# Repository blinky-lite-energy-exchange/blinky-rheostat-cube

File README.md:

# Blinky Rheostat Cube
The Blinky Rheostat Cube is a stepper motor drive that is designed to drive 12V bi-polar stepper motors using the high current [DRV8825 Stepper Motor Driver Carrier](https://www.pololu.com/product/2133). The DRV8825 is driven by a [Teensy LC](https://www.pjrc.com/teensy/teensyLC.html) micro-controller. The Teensy LC micro-controller communicates to the [Blinky Rheostat tray](https://github.com/blinky-lite-energy-exchange/blinky-rheostat-tray) with a serial Bluetooth connection very similar to the connection method described in the [Blinky Bus Cube](https://github.com/Blinky-Lite-Exchange/blinky-bus-cube) project.

<br>

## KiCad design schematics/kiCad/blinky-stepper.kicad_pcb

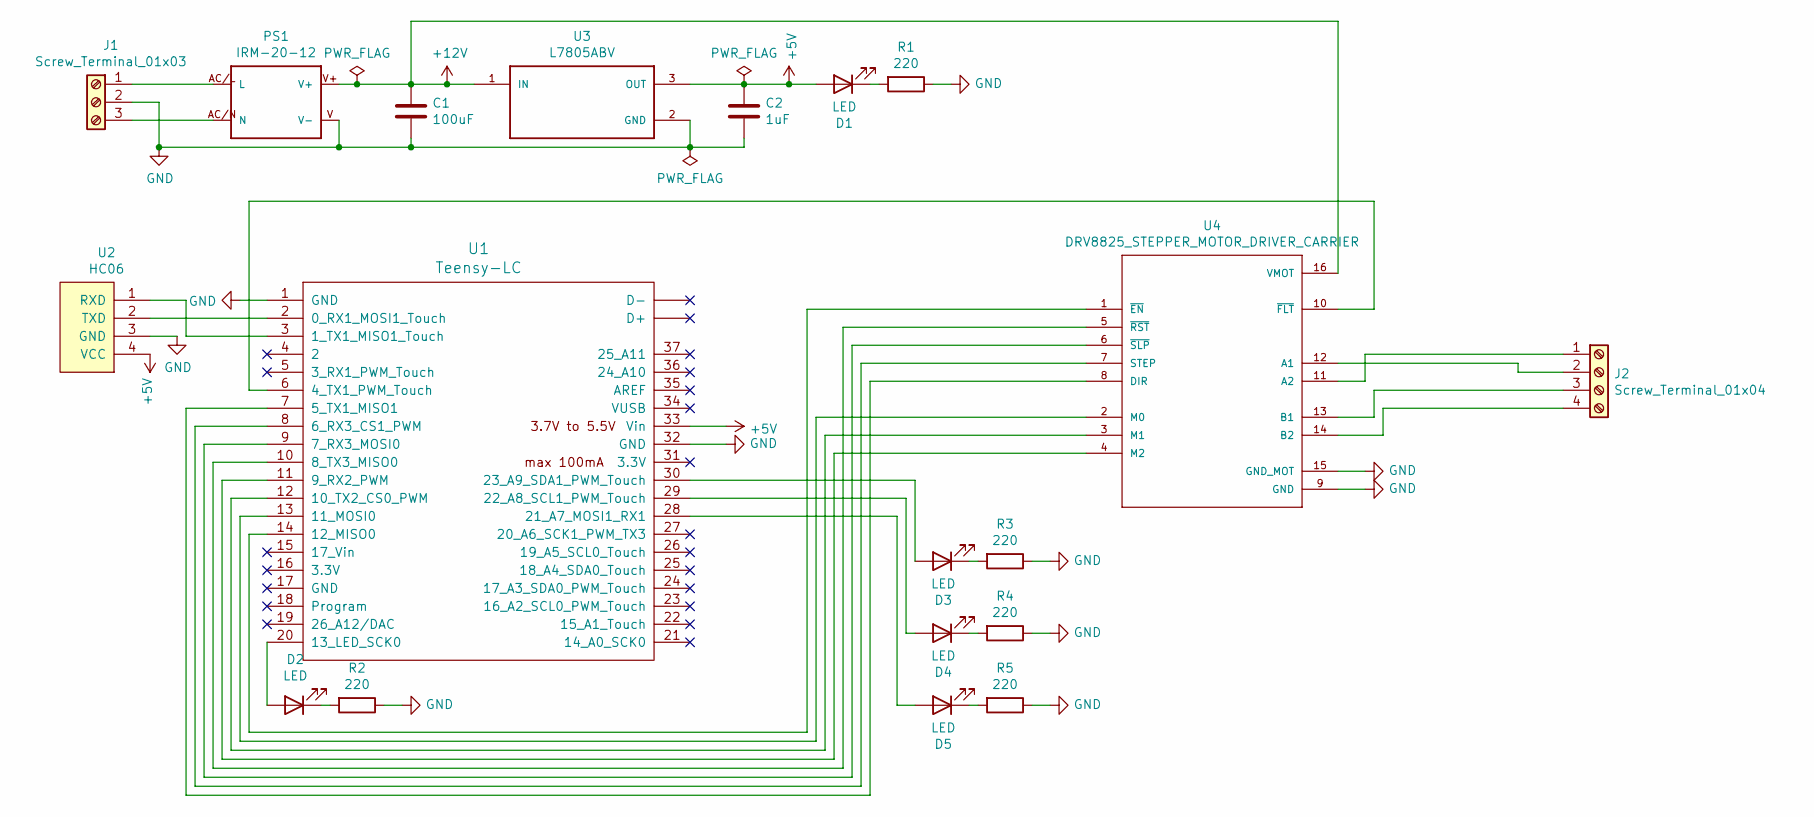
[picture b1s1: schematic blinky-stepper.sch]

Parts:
C1: 100uF; CP_Radial_D10.0mm_P5.00mm
C2: 1uF; C_1206_3216Metric_Pad1.42x1.75mm_HandSolder
D1, D2, D3, D4, D5: LED; LED_D5.0mm
J1: Screw_Terminal_01x03; TerminalBlock_bornier-3_P5.08mm
J2: Screw_Terminal_01x04; TerminalBlock_bornier-4_P5.08mm
PS1: IRM-20-12
R1, R2, R3, R4, R5: 220; R_1206_3216Metric_Pad1.42x1.75mm_HandSolder
U1: Teensy-LC; Teensy30_31_32_LC
U2: HC06
U3: L7805ABV; TO254P460X1020X1945-3P
U4: DRV8825_STEPPER_MOTOR_DRIVER_CARRIER; IC_DRV8825_STEPPER_MOTOR_DRIVER_CARRIER

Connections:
+5V: C2.1, D1.2 (A), U1.33 (Vin), U2.4 (VCC), U3.3 (OUT)
+12V: C1.1, PS1.V+, U3.1 (IN), U4.16 (VMOT)
GND: C1.2, C2.2, J1.2, PS1.V (V-), R1.1, R2.1, R3.1, R4.1, R5.1, U1.1 (GND), U1.32 (GND), U2.3 (GND), U3.2 (GND), U4.9 (GND), U4.15 (GND_MOT)
unnamed: D1.1 (K), R1.2
unnamed: D2.1 (K), R2.2
unnamed: D2.2 (A), U1.20 (13_LED_SCK0)
unnamed: D3.1 (K), R3.2
unnamed: D3.2 (A), U1.30 (23_A9_SDA1_PWM_Touch)
unnamed: D4.1 (K), R4.2
unnamed: D4.2 (A), U1.29 (22_A8_SCL1_PWM_Touch)
unnamed: D5.1 (K), R5.2
unnamed: D5.2 (A), U1.28 (21_A7_MOSI1_RX1)
unnamed: J1.1, PS1.AC/L (L)
unnamed: J1.3, PS1.AC/N (N)
unnamed: J2.1, U4.11 (A2)
unnamed: J2.2, U4.12 (A1)
unnamed: J2.3, U4.13 (B1)
unnamed: J2.4, U4.14 (B2)
unnamed: U1.2 (0_RX1_MOSI1_Touch), U2.2 (TXD)
unnamed: U1.3 (1_TX1_MISO1_Touch), U2.1 (RXD)
unnamed: U1.6 (4_TX1_PWM_Touch), U4.10 (~FLT~)
unnamed: U1.7 (5_TX1_MISO1), U4.8 (DIR)
unnamed: U1.8 (6_RX3_CS1_PWM), U4.7 (STEP)
unnamed: U1.9 (7_RX3_MOSI0), U4.6 (~SLP~)
unnamed: U1.10 (8_TX3_MISO0), U4.5 (~RST~)
unnamed: U1.11 (9_RX2_PWM), U4.4 (M2)
unnamed: U1.12 (10_TX2_CS0_PWM), U4.3 (M1)
unnamed: U1.13 (11_MOSI0), U4.2 (M0)
unnamed: U1.14 (12_MISO0), U4.1 (~EN~)

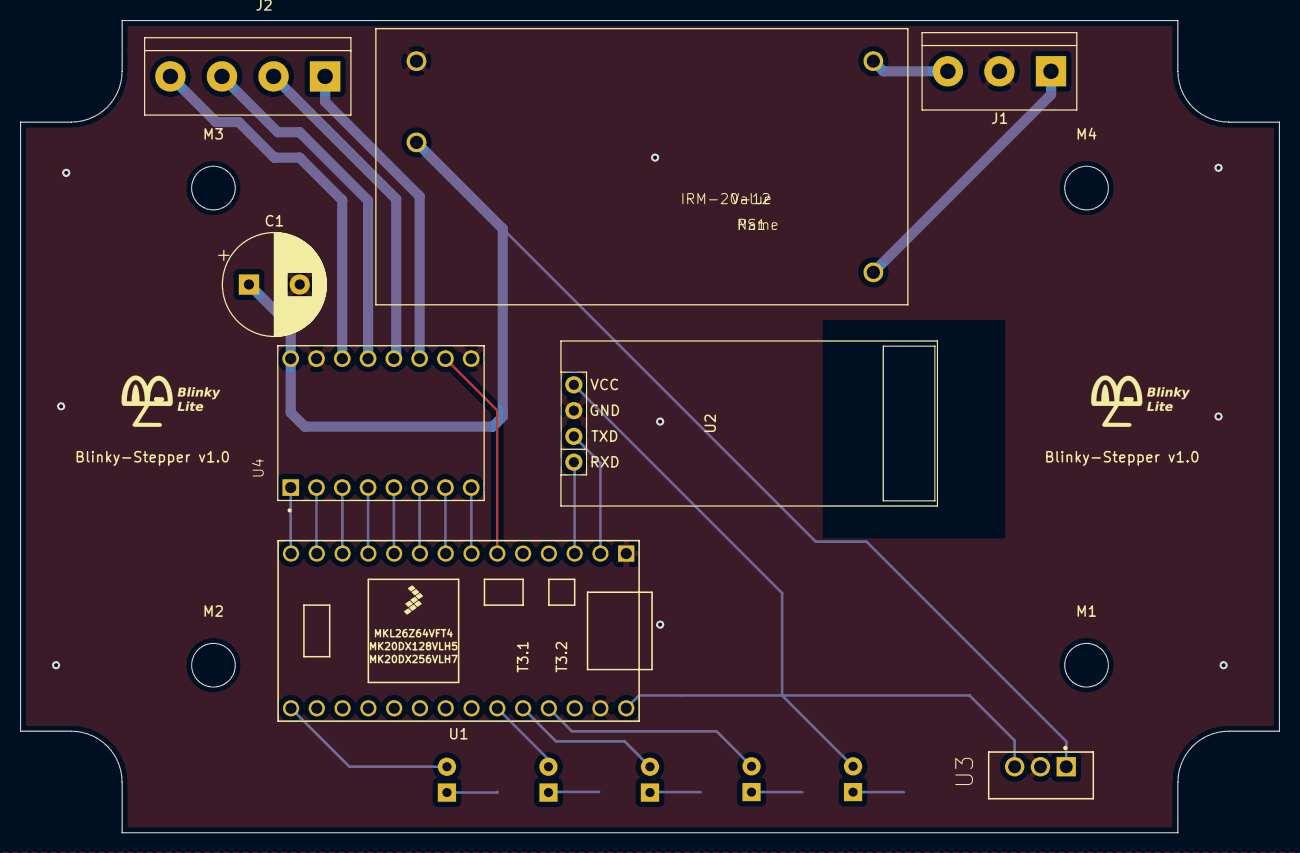
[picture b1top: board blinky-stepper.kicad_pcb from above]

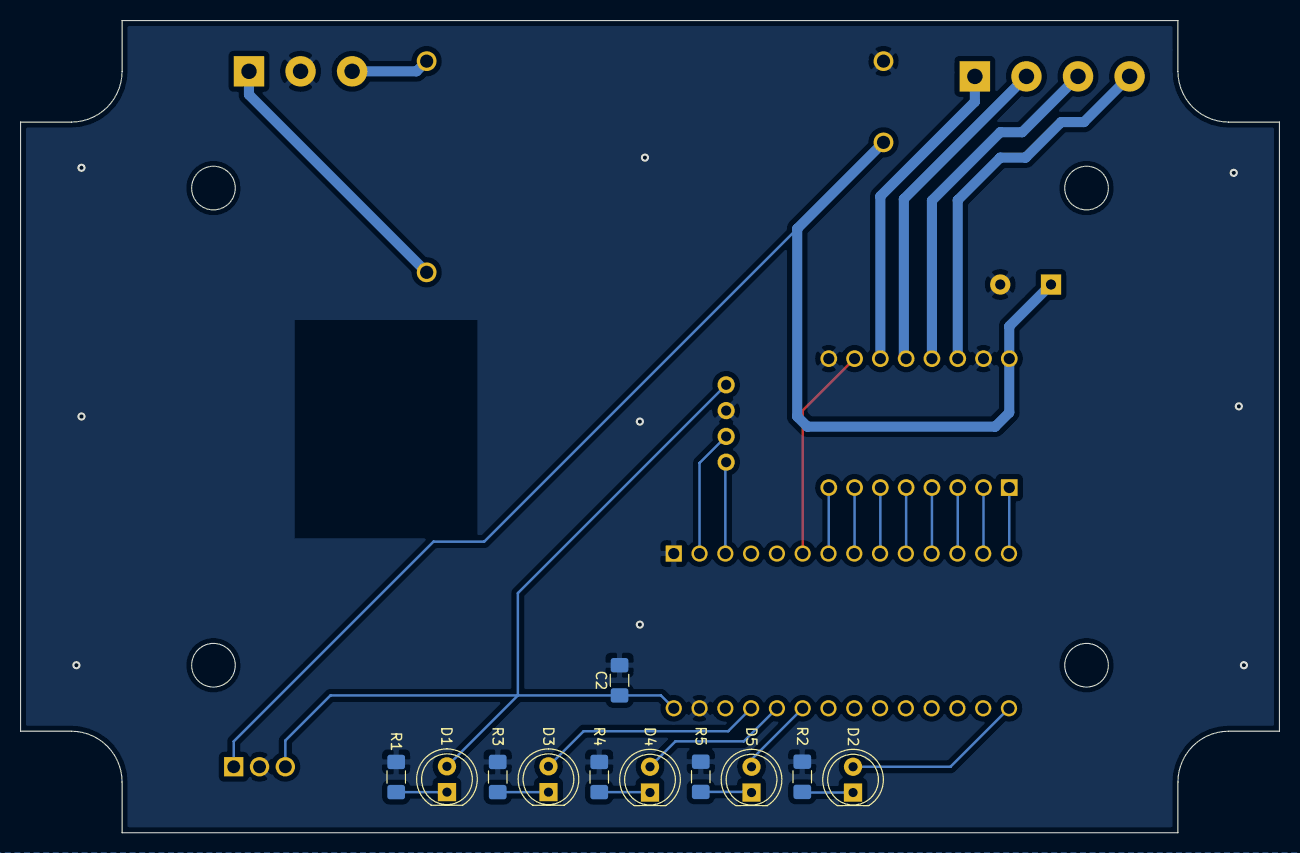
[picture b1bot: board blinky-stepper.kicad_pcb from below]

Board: 2 copper layers, 124.0 x 80.0 mm, 23 parts (11 on the bottom side), 29 nets.

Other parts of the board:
M1, M2, M3, M4: MountingHole_4.3mm_M4

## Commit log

2020-10-26 working prototype code
2020-10-27 pcb finished
2020-12-07 before editing
2020-12-07 test program working
2020-12-08 allow negative steps
2020-12-10 working with tray
2021-01-16 baud rate at 115200
2021-10-22 new cube code with modbus
2022-01-13 implemented blinky-bus
2022-08-23 new blinky bus and set location to new value
